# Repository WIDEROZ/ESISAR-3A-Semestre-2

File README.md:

# I - Install all the repository
#### $1^{st}$ Step - Clone
##### ssh
```bash
git clone git@github.com:WIDEROZ/ESISAR-3A-Semestre-2.git
```

##### HTTPS
```bash
git clone https://github.com/WIDEROZ/ESISAR-3A-Semestre-2.git
```

#### $2^{nd}$ Step - Update submodules
```bash
cd ESISAR-3A-Semestre-2
git submodule update --init --recursive
```

## II - Install the `.obsidian` folder
#### $1^{st}$ Step - Clone
##### ssh
```bash
git clone git@github.com:WIDEROZ/ESISAR-3A-Semestre-2.git
```

##### HTTPS
```bash
git clone https://github.com/WIDEROZ/ESISAR-3A-Semestre-2.git
```

#### $2^{nd}$ Step - Update `.obsidian`
```bash
cd ESISAR-3A-Semestre-2
git submodule update --init .obsidian
```

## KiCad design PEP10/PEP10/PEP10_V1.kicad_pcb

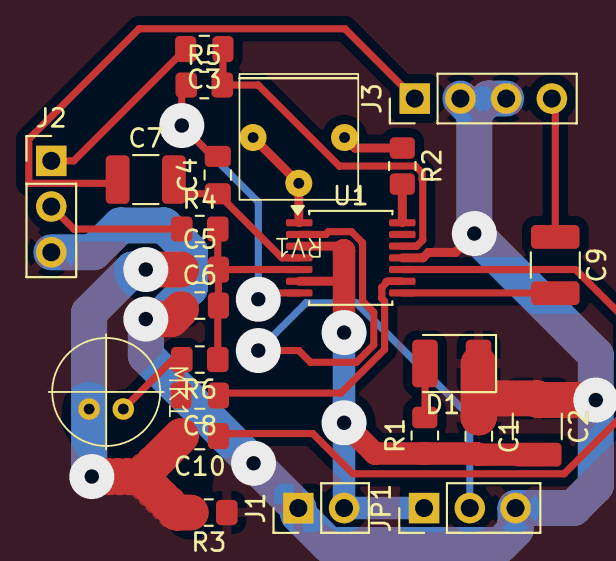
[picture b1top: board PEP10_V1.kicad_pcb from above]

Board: 2 copper layers, 24 parts (0 on the bottom side), 20 nets.

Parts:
C1, C3, C4, C5, C6, C8, C10: C; C_0805_2012Metric_Pad1.18x1.45mm_HandSolder
C2, C7, C9: C; C_1210_3225Metric_Pad1.33x2.70mm_HandSolder
D1: LED; LED_1210_3225Metric_Pad1.42x2.65mm_HandSolder
J1: Conn_01x02_Pin; PinHeader_1x02_P2.54mm_Vertical
J2: Conn_01x03_Pin; PinHeader_1x03_P2.54mm_Vertical
J3: Conn_01x04_Pin; PinHeader_1x04_P2.54mm_Vertical
JP1: Jumper_3_Bridged12; PinHeader_1x03_P2.54mm_Vertical
MK1: Microphone_Condenser; MicroCondenserPEP
R1, R2, R3, R4, R5, R6: R; R_0805_2012Metric_Pad1.20x1.40mm_HandSolder
RV1: R_Potentiometer; TrimmerPEP
U1: TSSOP-14_4.4x5mm_P0.65mm

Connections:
/AUX: C3.1, R5.2, U1.12 (AUX-IN)
/Vcc: C1.2, C2.2, J1.2, JP1.1 (A), R1.1, U1.3 (~SDN), U1.6 (VCC)
GND: C1.1, C2.1, C6.1, D1.1 (K), J1.1, J2.3, J3.2, J3.3, JP1.3 (B), R3.1, U1.11 (GND)
GNDPWR: C5.1, C10.2, MK1.1 (-), R3.2
unnamed: D1.2 (A), R1.2
unnamed: C3.2, J2.1
unnamed: J2.2, R4.1
unnamed: C7.1, J3.1
unnamed: C9.1, J3.4
unnamed: JP1.2 (C), U1.2 (~INT/AUX)
unnamed: C8.2, MK1.2 (+), R6.2
unnamed: R2.1, RV1.1
unnamed: C4.2, R5.1, U1.7 (ADJ)
unnamed: C5.2, C6.2, R4.2, R6.1, U1.5 (BIAS)
unnamed: R2.2, U1.14 (G1)
unnamed: RV1.2, RV1.3, U1.1 (G2)
unnamed: C8.1, U1.9 (IN+)
unnamed: C10.1, U1.10 (IN-)
unnamed: C4.1, C7.2, U1.4 (OP)
unnamed: C9.2, U1.8 (~OP)

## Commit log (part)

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2026-02-13 obsidian-auto-push : 2026-02-13 11:42:31
2026-02-13 obsidian-auto-push : 2026-02-13 11:52:37
2026-02-13 obsidian-auto-push : 2026-02-13 12:12:48
2026-02-13 obsidian-auto-push : 2026-02-13 14:02:38
2026-02-13 obsidian-auto-push : 2026-02-13 14:22:53
2026-02-13 obsidian-auto-push : 2026-02-13 14:33:01
2026-02-13 obsidian-auto-push : 2026-02-13 14:53:15
2026-02-13 obsidian-auto-push : 2026-02-13 15:03:21
2026-02-13 obsidian-auto-push : 2026-02-13 15:23:35
2026-02-13 obsidian-auto-push : 2026-02-13 15:57:58
2026-02-13 obsidian-auto-push : 2026-02-13 16:58:19
2026-02-13 obsidian-auto-push : 2026-02-13 17:18:32
2026-02-13 obsidian-auto-push : 2026-02-13 19:39:07
2026-02-14 obsidian-auto-push : 2026-02-14 19:40:54
2026-02-15 obsidian-auto-push : 2026-02-15 12:01:13
2026-02-24 obsidian-auto-push : 2026-02-24 08:48:17
2026-02-24 obsidian-auto-push : 2026-02-24 09:08:28
2026-02-24 obsidian-auto-push : 2026-02-24 09:18:33
2026-02-24 obsidian-auto-push : 2026-02-24 09:38:44
2026-02-24 obsidian-auto-push : 2026-02-24 09:48:49
2026-02-24 obsidian-auto-push : 2026-02-24 10:08:59
2026-02-24 obsidian-auto-push : 2026-02-24 10:36:58
2026-02-24 obsidian-auto-push : 2026-02-24 10:57:10
2026-02-24 obsidian-auto-push : 2026-02-24 11:17:21
2026-02-24 obsidian-auto-push : 2026-02-24 11:27:26
2026-02-24 obsidian-auto-push : 2026-02-24 11:47:37
2026-02-24 obsidian-auto-push : 2026-02-24 11:57:42
2026-02-25 Java + TP AU360
2026-02-25 obsidian-auto-push : 2026-02-25 18:28:33
2026-02-25 obsidian-auto-push : 2026-02-25 19:34:27
2026-02-25 obsidian-auto-push : 2026-02-25 19:54:42
2026-02-25 obsidian-auto-push : 2026-02-25 20:04:51
2026-02-25 obsidian-auto-push : 2026-02-25 20:25:10
2026-02-25 obsidian-auto-push : 2026-02-25 20:35:19
2026-02-25 obsidian-auto-push : 2026-02-25 20:55:39
2026-02-25 obsidian-auto-push : 2026-02-25 21:36:14
2026-02-26 obsidian-auto-push : 2026-02-26 08:48:27
2026-02-26 obsidian-auto-push : 2026-02-26 08:58:36
2026-02-26 obsidian-auto-push : 2026-02-26 09:18:50
2026-02-26 obsidian-auto-push : 2026-02-26 09:39:05
2026-02-26 obsidian-auto-push : 2026-02-26 09:49:12
2026-02-26 obsidian-auto-push : 2026-02-26 10:09:25
2026-02-26 obsidian-auto-push : 2026-02-26 10:19:31
2026-02-26 obsidian-auto-push : 2026-02-26 11:13:55
2026-02-26 obsidian-auto-push : 2026-02-26 11:28:23
2026-02-26 obsidian-auto-push : 2026-02-26 15:52:36
2026-02-26 obsidian-auto-push : 2026-02-26 16:12:57
2026-02-26 obsidian-auto-push : 2026-02-26 16:23:05
2026-02-26 obsidian-auto-push : 2026-02-26 16:43:21
2026-02-26 obsidian-auto-push : 2026-02-26 16:53:30
2026-02-26 obsidian-auto-push : 2026-02-26 17:13:46
2026-02-26 obsidian-auto-push : 2026-02-26 17:23:54
2026-02-26 obsidian-auto-push : 2026-02-26 17:44:11
2026-02-26 obsidian-auto-push : 2026-02-26 18:04:27
2026-02-26 obsidian-auto-push : 2026-02-26 18:14:35
2026-02-26 obsidian-auto-push : 2026-02-26 18:44:57
2026-02-26 obsidian-auto-push : 2026-02-26 18:55:05
2026-02-26 obsidian-auto-push : 2026-02-26 19:15:22
2026-02-26 obsidian-auto-push : 2026-02-26 19:25:30
2026-02-26 obsidian-auto-push : 2026-02-26 19:45:46
2026-02-26 obsidian-auto-push : 2026-02-26 20:06:10
2026-02-26 obsidian-auto-push : 2026-02-26 20:16:18
2026-02-26 obsidian-auto-push : 2026-02-26 20:36:35
2026-02-26 obsidian-auto-push : 2026-02-26 20:46:44
2026-02-26 obsidian-auto-push : 2026-02-26 21:07:02
2026-02-26 obsidian-auto-push : 2026-02-26 21:17:37
2026-02-26 obsidian-auto-push : 2026-02-26 21:51:04
2026-02-27 obsidian-auto-push : 2026-02-27 08:46:12
2026-02-27 obsidian-auto-push : 2026-02-27 09:16:30
2026-02-27 obsidian-auto-push : 2026-02-27 09:36:44
2026-02-27 obsidian-auto-push : 2026-02-27 09:46:51
2026-02-27 obsidian-auto-push : 2026-02-27 12:12:51
2026-02-27 obsidian-auto-push : 2026-02-27 13:54:58
2026-02-27 obsidian-auto-push : 2026-02-27 14:22:54
2026-02-27 obsidian-auto-push : 2026-02-27 14:43:05
2026-02-27 obsidian-auto-push : 2026-02-27 15:03:23
2026-02-27 obsidian-auto-push : 2026-02-27 15:23:39
2026-02-27 obsidian-auto-push : 2026-02-27 15:33:46
2026-02-27 obsidian-auto-push : 2026-02-27 15:54:01
2026-02-27 obsidian-auto-push : 2026-02-27 16:04:09
2026-03-01 obsidian-auto-push : 2026-03-01 10:54:21
2026-03-01 obsidian-auto-push : 2026-03-01 11:04:30
2026-03-01 obsidian-auto-push : 2026-03-01 11:34:29
2026-03-01 obsidian-auto-push : 2026-03-01 11:54:47
2026-03-01 obsidian-auto-push : 2026-03-01 12:04:56
2026-03-01 obsidian-auto-push : 2026-03-01 12:25:12
2026-03-01 obsidian-auto-push : 2026-03-01 13:05:36
2026-03-01 obsidian-auto-push : 2026-03-01 13:25:52
2026-03-01 obsidian-auto-push : 2026-03-01 13:46:06
2026-03-01 obsidian-auto-push : 2026-03-01 14:06:23
2026-03-01 obsidian-auto-push : 2026-03-01 15:17:20
2026-03-01 obsidian-auto-push : 2026-03-01 15:27:29
2026-03-01 obsidian-auto-push : 2026-03-01 15:58:01
2026-03-01 obsidian-auto-push : 2026-03-01 16:08:21
2026-03-01 obsidian-auto-push : 2026-03-01 17:09:18
2026-03-01 obsidian-auto-push : 2026-03-01 17:19:28
2026-03-01 obsidian-auto-push : 2026-03-01 17:39:49
2026-03-01 obsidian-auto-push : 2026-03-01 17:49:59
2026-03-01 obsidian-auto-push : 2026-03-01 18:14:58
2026-03-01 obsidian-auto-push : 2026-03-01 18:45:24
2026-03-01 obsidian-auto-push : 2026-03-01 18:55:39
2026-03-03 README
2026-03-03 obsidian-auto-push : 2026-03-03 09:15:36
2026-03-03 CRE changed
2026-03-03 .obsidian commit
2026-03-03 obsidian-auto-push : 2026-03-03 22:23:37
2026-03-04 obsidian-auto-push : 2026-03-04 08:53:45
2026-03-04 obsidian-auto-push : 2026-03-04 09:03:51
2026-03-04 obsidian-auto-push : 2026-03-04 09:23:36
2026-03-04 obsidian-auto-push : 2026-03-04 09:33:41
2026-03-04 obsidian-auto-push : 2026-03-04 09:53:53
2026-03-04 obsidian-auto-push : 2026-03-04 10:03:58
2026-03-04 obsidian-auto-push : 2026-03-04 10:44:32
2026-03-04 obsidian-auto-push : 2026-03-04 11:04:39
2026-03-04 obsidian-auto-push : 2026-03-04 11:14:45
2026-03-04 obsidian-auto-push : 2026-03-04 11:55:04
2026-03-04 obsidian-auto-push : 2026-03-04 12:05:11
2026-03-05 obsidian-auto-push : 2026-03-05 09:24:22
2026-03-05 obsidian-auto-push : 2026-03-05 09:34:30
2026-03-05 obsidian-auto-push : 2026-03-05 09:54:49
2026-03-05 obsidian-auto-push : 2026-03-05 10:15:07
2026-03-05 obsidian-auto-push : 2026-03-05 10:25:15
2026-03-05 obsidian-auto-push : 2026-03-05 10:45:33
2026-03-05 obsidian-auto-push : 2026-03-05 15:24:31
2026-03-05 CRE update
2026-03-06 obsidian-auto-push : 2026-03-06 08:37:07
2026-03-06 obsidian-auto-push : 2026-03-06 10:55:11
2026-03-06 obsidian-auto-push : 2026-03-06 11:05:16
2026-03-06 obsidian-auto-push : 2026-03-06 14:10:12
2026-03-06 obsidian-auto-push : 2026-03-06 14:40:29
2026-03-06 obsidian-auto-push : 2026-03-06 14:50:35
2026-03-06 obsidian-auto-push : 2026-03-06 15:10:47
2026-03-06 obsidian-auto-push : 2026-03-06 15:20:53
2026-03-06 obsidian-auto-push : 2026-03-06 15:59:44
2026-03-06 obsidian-auto-push : 2026-03-06 16:09:49
2026-03-06 obsidian-auto-push : 2026-03-06 16:30:00
2026-03-06 obsidian-auto-push : 2026-03-06 16:50:12
2026-03-06 obsidian-auto-push : 2026-03-06 17:00:17
2026-03-06 obsidian-auto-push : 2026-03-06 22:33:00
2026-03-06 obsidian-auto-push : 2026-03-06 23:03:11
2026-03-06 obsidian-auto-push : 2026-03-06 23:23:30
2026-03-06 obsidian-auto-push : 2026-03-06 23:33:38
2026-03-06 obsidian-auto-push : 2026-03-06 23:53:50
2026-03-06 obsidian-auto-push : 2026-03-07 00:14:03
2026-03-06 obsidian-auto-push : 2026-03-07 00:24:10
2026-03-06 obsidian-auto-push : 2026-03-07 00:44:24
2026-03-09 obsidian-auto-push : 2026-03-09 09:23:45
2026-03-09 obsidian-auto-push : 2026-03-09 14:47:05
2026-03-10 obsidian-auto-push : 2026-03-10 11:41:00
2026-03-10 obsidian-auto-push : 2026-03-10 15:25:56
2026-03-10 obsidian-auto-push : 2026-03-11 00:23:10
2026-03-11 obsidian-auto-push : 2026-03-11 08:34:16
2026-03-11 obsidian-auto-push : 2026-03-11 08:54:39
2026-03-11 obsidian-auto-push : 2026-03-11 09:04:45
2026-03-11 obsidian-auto-push : 2026-03-11 09:24:58
2026-03-11 obsidian-auto-push : 2026-03-11 09:35:05
2026-03-11 obsidian-auto-push : 2026-03-11 10:52:04
2026-03-11 obsidian-auto-push : 2026-03-11 18:10:03
2026-03-12 obsidian-auto-push : 2026-03-11 11:16:39
2026-03-13 VLAN
2026-03-14 obsidian-auto-push : 2026-03-14 01:26:40
2026-03-16 obsidian commit : 2026-03-16 15:10:38
2026-03-17 obsidian-auto-push : 2026-03-17 11:07:24
2026-03-17 obsidian-auto-push : 2026-03-17 11:27:36
2026-03-17 obsidian-auto-push : 2026-03-17 11:37:42
2026-03-17 obsidian-auto-push : 2026-03-17 14:31:05
2026-03-17 obsidian-auto-push : 2026-03-17 14:51:19
2026-03-17 obsidian-auto-push : 2026-03-17 15:01:25
2026-03-17 obsidian-auto-push : 2026-03-17 15:48:06
2026-03-17 obsidian-auto-push : 2026-03-17 15:58:13
2026-03-17 obsidian-auto-push : 2026-03-17 16:18:28
2026-03-17 obsidian-auto-push : 2026-03-17 16:28:35
2026-03-17 obsidian-auto-push : 2026-03-17 16:48:49
2026-03-17 obsidian-auto-push : 2026-03-17 17:09:04
2026-03-17 obsidian-auto-push : 2026-03-17 17:19:13
2026-03-18 obsidian-auto-push : 2026-03-18 08:29:23
2026-03-18 obsidian-auto-push : 2026-03-18 08:39:28
2026-03-18 obsidian-auto-push : 2026-03-18 08:59:40
2026-03-18 obsidian-auto-push : 2026-03-18 09:09:45
2026-03-18 obsidian-auto-push : 2026-03-18 09:29:56
2026-03-18 obsidian-auto-push : 2026-03-18 09:50:08
2026-03-18 obsidian-auto-push : 2026-03-18 10:00:14
2026-03-18 obsidian-auto-push : 2026-03-18 10:35:25
2026-03-18 obsidian-auto-push : 2026-03-18 10:45:30
2026-03-18 obsidian-auto-push : 2026-03-18 11:05:42
2026-03-18 obsidian-auto-push : 2026-03-18 11:15:49
2026-03-18 obsidian-auto-push : 2026-03-18 11:36:02
2026-03-18 obsidian-auto-push : 2026-03-18 11:46:08
2026-03-18 obsidian-auto-push : 2026-03-18 12:38:28
2026-03-20 obsidian-auto-push : 2026-03-20 10:50:35
2026-03-20 obsidian-auto-push : 2026-03-20 11:00:42
2026-03-20 obsidian-auto-push : 2026-03-20 11:20:56
2026-03-20 obsidian-auto-push : 2026-03-20 11:31:03
2026-03-20 obsidian-auto-push : 2026-03-20 11:51:17
2026-03-20 obsidian-auto-push : 2026-03-20 12:01:24
2026-03-20 obsidian-auto-push : 2026-03-20 13:57:22
2026-03-20 obsidian-auto-push : 2026-03-20 14:17:33
2026-03-20 obsidian-auto-push : 2026-03-20 14:27:39
2026-03-20 obsidian-auto-push : 2026-03-20 14:47:51
2026-03-20 obsidian-auto-push : 2026-03-20 14:57:57
2026-03-20 obsidian-auto-push : 2026-03-20 16:11:18
2026-03-21 obsidian-auto-push : 2026-03-21 13:05:12
2026-03-21 obsidian-auto-push : 2026-03-21 14:25:34
2026-03-21 obsidian-auto-push : 2026-03-21 14:45:42
2026-03-21 obsidian-auto-push : 2026-03-21 14:55:47
2026-03-21 obsidian-auto-push : 2026-03-21 15:15:55
2026-03-21 obsidian-auto-push : 2026-03-21 15:25:59
2026-03-22 obsidian-auto-push : 2026-03-22 13:24:26
2026-03-22 obsidian-auto-push : 2026-03-22 13:34:30
2026-03-22 obsidian-auto-push : 2026-03-22 14:04:41
2026-03-22 obsidian-auto-push : 2026-03-22 14:24:50
2026-03-22 obsidian-auto-push : 2026-03-22 14:34:54
2026-03-22 obsidian-auto-push : 2026-03-22 15:15:07
2026-03-22 obsidian-auto-push : 2026-03-22 15:25:11
2026-03-22 obsidian commit : 2026-03-22 15:37:16
2026-03-22 obsidian-auto-push : 2026-03-22 16:21:21
2026-03-22 obsidian-auto-push : 2026-03-22 16:41:30
2026-03-23 obsidian-auto-push : 2026-03-23 09:51:33
2026-03-23 obsidian-auto-push : 2026-03-23 10:12:34
2026-03-23 obsidian-auto-push : 2026-03-23 10:32:46
2026-03-23 obsidian-auto-push : 2026-03-23 10:42:52
2026-03-23 obsidian-auto-push : 2026-03-23 11:03:04
2026-03-23 obsidian-auto-push : 2026-03-23 11:13:10
2026-03-23 obsidian-auto-push : 2026-03-23 15:08:35
2026-03-23 obsidian-auto-push : 2026-03-23 15:28:49
2026-03-24 obsidian-auto-push : 2026-03-24 08:43:45
2026-03-24 obsidian-auto-push : 2026-03-24 09:24:00
2026-03-24 obsidian-auto-push : 2026-03-24 10:04:15
2026-03-24 obsidian-auto-push : 2026-03-24 10:24:27
2026-03-26 feur
2026-04-01 MT360
2026-04-02 AU + SN + CRE
2026-04-14 AU360 + IN360 + MT360
2026-05-08 IN360
2026-05-10 MT360 Oral
2026-05-17 RÉvisions
2026-05-20 partiels
2026-05-23 Revise title and enhance introduction on technology and creativity
    Revised the title and improved the introduction of the document discussing the impact of technology on creativity, particularly in relation to generative AI.
2026-05-23 Rename Is technology helping creativity or destroying it?.md to Is technology helping creativity or destroying it.md
2026-05-25 Images
2026-06-14 gitignore java_fx
2026-06-14 gitignore javafx
